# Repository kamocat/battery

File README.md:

# battery
Single-cell lipo battery monitor

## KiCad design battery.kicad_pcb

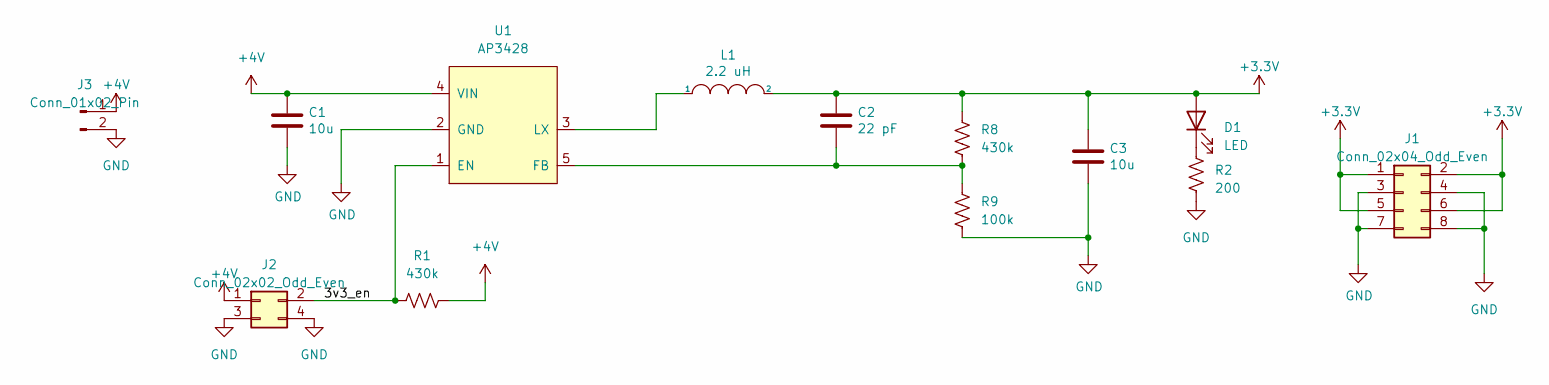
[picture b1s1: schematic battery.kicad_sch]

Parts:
C1, C3: 10u; C_0805_2012Metric
C2: 22 pF; C_0603_1608Metric
D1: LED; LED_0603_1608Metric
J1: Conn_02x04_Odd_Even; PinHeader_2x04_P2.54mm_Vertical
J2: Conn_02x02_Odd_Even; PinHeader_2x02_P2.54mm_Vertical
J3: Conn_01x02_Pin; JST_PH_S2B-PH-K_1x02_P2.00mm_Horizontal
L1: 2.2 uH; L_0805_2012Metric
R1, R8: 430k; R_0603_1608Metric
R2: 200; R_0603_1608Metric
R9: 100k; R_0603_1608Metric
U1: AP3428; SOT-23-5

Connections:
+3.3V: C2.1, C3.1, D1.2 (A), J1.1, J1.2, J1.5, J1.6, L1.2, R8.1
+4V: C1.1, J2.1, J3.1, R1.2, U1.4 (VIN)
/3v3_en: J2.2, R1.1, U1.1 (EN)
GND: C1.2, C3.2, J1.3, J1.4, J1.7, J1.8, J2.3, J2.4, J3.2, R2.2, R9.2, U1.2 (GND)
unnamed: D1.1 (K), R2.1
unnamed: C2.2, R8.2, R9.1, U1.5 (FB)
unnamed: L1.1, U1.3 (LX)

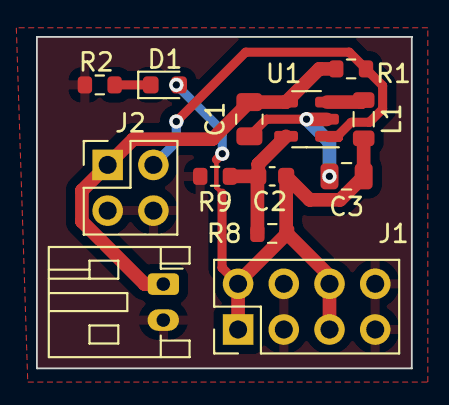
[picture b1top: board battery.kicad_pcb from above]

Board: 2 copper layers, 20.8 x 18.4 mm, 13 parts (0 on the bottom side), 7 nets.

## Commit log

2022-03-10 Initial schematic
2022-03-11 tight regulator layout
2022-03-11 High-side switch for solar cell.
    Need to place the uC interconnect - maybe a surface-mount connector will
    do
2022-03-11 Routed uC interconnect
2022-03-11 Changed to single transistor for solar disconnect
2022-03-11 Completed silkscreen, sent board to fab
2022-03-11 Added order BOM for v0.1
2023-03-21 Simplified board, switched to JST PH connector
    Also upgraded to KiCad 7.0
2023-03-21 Silkscreen adjustements
